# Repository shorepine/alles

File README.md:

# Alles - the mesh synthesizer

 [ **Chat about Alles on our Discord!**](https://discord.gg/TzBFkUb8pG)

**Check out this video!**

**Alles** is a many-speaker distributed mesh synthesizer that responds over WiFi. Each synth -- there can be hundreds in a mesh -- supports up to 120 additive oscillators, with filters, modulation / LFOs and ADSRs per oscillator. The mesh of speakers can be composed of any combination of our custom hardware speakers or programs running on computers. The software and hardware are open source: you can build it yourself or buy a PCB from us. 

The synthesizers automatically form a mesh and listen to multicast WiFi messages. You can control the mesh from a host computer using any programming language or environments like Max or Pd. 

We intended their first use as distributed / spatial version of an [Alles Machine](https://en.wikipedia.org/wiki/Bell_Labs_Digital_Synthesizer) / [Atari AMY](https://www.atarimax.com/jindroush.atari.org/achamy.html) additive synthesizer where each speaker represents up to 64 partials, all controlled as a group or individually. But you can just treat them as dozens of individual synthesizers and do whatever you want with them. It's pretty fun!

Want to try it today? [Build your own Alles](#diy-alles), or [install the software version](#using-it----software-alles
), and then read our [getting started tutorial!](https://github.com/shorepine/alles/tree/main/getting-started.md)

## Synthesizer specs

Each individual synth is powered by the [AMY synthesizer library](https://github.com/shorepine/amy/blob/main/README.md), you can read more details there. 

## Using it -- hardware Alles

On first boot, each hardware speaker will create a captive wifi network called `alles-synth-X` where X is some ID of the synth. Join it (preferably on a mobile device), and you should get redirected to a captive wifi setup page. If not, go to `http://10.10.0.1` in your browser after joining the network. Once you tell each synth what the wifi SSID and password you want it to join are, it will reboot. You only need to do that once per synth.

## Using it -- software Alles

If you don't want to build or buy an Alles speaker, you can run Alles locally on your computer(s), as many as you want. As long as each copy of the software is running within the same network, they will automatically form in the mesh just like the hardware speakers. And the hardware and software speakers can be used interchangeably.

To build and run `alles` on a computer, simply clone this repository and

```bash
$ cd alles/main
$ make
$ ./alles
$ ./alles -h # shows all the useful commandline parameters, like changing which channel/sound card, or source IP address
```

## Controlling the mesh

**Check out our brand new [Getting Started](https://github.com/shorepine/alles/tree/main/getting-started.md) page for a tutorial!**

You can control every synth on the mesh from a single host, using UDP over WiFi. You can address any synth in the mesh or all of them at once with one message, or use groups. This method can be used in music environments like Max or Pd, or by musicians or developers using languages like Python, or for plug-in developers who want to bridge Alles's full features to DAWs.

Alles's wire protocol is a series of numbers delimited by ascii characters that define all possible parameters of an oscillator. This is a design decision intended to make using Alles from any sort of environment as easy as possible, with no data structure or parsing overhead on the client. It's also readable and compact, far more expressive than MIDI and can be sent over network links, UARTs, or as arguments to functions or commands. 

Alles accepts commands in ASCII, each command separated with a `Z` (you can group multiple messages in one, to avoid network overhead if that's your transport). Like so:

```
v0w4f440.0l0.9Z
```

See [AMY's readme](https://github.com/shorepine/amy/blob/main/README.md) for the full list of synth parameters.

## alles.py 

Alles comes with its own full-featured client, written in Python. Feel free to adapt it or use it in your own clients. It can be seen as documentation, an API as well as a testing suite. You simply `import alles` and can control the entire mesh.

```bash
$ python3
>>> import alles
>>> alles.drums() # plays a drum pattern on all synths
>>> alles.drums(client=2) # just on one 
```

To see more examples, check out our brand new [Getting Started](https://github.com/shorepine/alles/tree/main/getting-started.md) page.

## Addressing individual synthesizers

By default, a message is played by all booted synthesizers. But you can address them individually or in groups using the `client` parameter.

The synthesizers form a mesh that self-identify who is running. They get auto-addressed `client_id`s starting at 0 through 255. The first synth to be booted in the mesh gets `0`, then `1`, and so on. If a synth is shut off or otherwise no longer sends a heartbeat signal to the mesh, the `client_ids` will reform so that they are always contiguous. A synth may take 10-20 seconds to join the mesh and get assigned a `client_id` after booting, but it will immediately receive messages sent to all synths. 

The `client` parameter wraps around given the number of booted synthesizers to make it easy on the composer. If you have 6 booted synths, a `client` of 0 only reaches the first synth, `1` only reaches the 2nd synth, and a client of `7` reaches the 2nd synth (`7 % 6 = 1`). 

Setting `client` to a number greater than 255 allows you to address groups. For example, a `client` of 257 performs the following check on each booted synthesizer: `my_client_id % (client-255) == 0`. This would only address every other synthesizer. A `client` of 259 would address every fourth synthesizer, and so on.

You can read the heartbeat messages on your host if you want to enumerate the synthesizers locally, see `sync` below. 

## Timing & latency

Alles is not designed as a low latency real-time performance instrument, where your actions have an immediate effect on the sound. Changes you make on the host will take a fixed latency -- currently set at 1000ms by default -- to get to every synth. This fixed latency ensures that messages arrive to every synth -- both ESP32 based and those running on computers -- in the mesh in time to play in perfect sync, even though Wi-Fi's transmission latency varies widely. This allows you to have millisecond-accurate timing in your performance across dozens of speakers in a large space.

Your host should send along the `time` parameter of the relative time when you expect the sound to play. I'd suggest using the number of milliseconds since your host started, e.g. in Python:

```python
def millis():
    d = datetime.datetime.now()
    return int((datetime.datetime.utcnow() - datetime.datetime(d.year, d.month, d.day)).total_seconds()*1000)
```

If you're using `alles.py`, we do this for you!

If using Max, use the `cpuclock` object as the `time` parameter.

The first time you send a message with `time` the synth mesh uses it to figure out the delta between its time and your expected time. (If you never send a time parameter, you're at the mercy of WiFi jitter.) Further messages will be millisecond accurate message-to-message, but with the fixed latency. You can adapt `time` per client if you want to account for speed-of-sound delay. 

The `time` parameter is not meant to schedule things far in the future on the clients. If you send a new `time` that is outside 20,000ms from its expected delta, the clock base will re-compute. Your host should be the main "sequencer" and keep track of performance state and future events. 

Latency is adjustable, if you are comfortable with your network you can set it lower, or if using a local (127.0.0.1) connection, or directly sending messages in code, you can set it to 0. 

## Enumerating synths

The `sync` command (see `alles.sync()`) triggers an immediate response back from each on-line synthesizer. The response looks like `_s65201i4c248y2`, where s is the time on the client, i is the index it is responding to, y has battery status (for versions that support that) and c is the client id. This lets you build a map of not only each booted synthesizer, but if you send many messages with different indexes, will also let you figure the round-trip latency for each one along with the reliability. 

## WiFi & reliability for performances

UDP multicast is naturally 'lossy' -- there is no guarantee that a message will be received by a synth. Depending on a lot of factors, but most especially your wireless router and the presence of other devices, that reliability can sometimes go as low as 70%. For performance purposes, I highly suggest using a dedicated wireless router instead of an existing WiFi network. You'll want to be able to turn off many "quality of service" features (these prioritize a randomly chosen synth and will make sync hard to work with), and you'll want to in the best case only have synthesizers as direct WiFi clients. An easy way to do this is to set up a dedicated wireless router but not wire any internet into it. Connect your laptop or host machine to the router over a wired connection (via a USB-ethernet adapter if you need one), but keep your laptop's wifi or other internet network active. In your controlling software, you simply set the source network address to send and receive multicast packets from. `alles_util.py` has setup code for this. This will keep your host machine on its normal network but allow you to control the synths from a second interface.

If you're in a place where you can't control your network, you can mitigate reliability by simply sending messages N times. Sending multiple duplicate messages (with the same `time` parameter) do not have any adverse effect on the synths.

## Clients

Minimal Python example:

```python
import socket
multicast_group = ('232.10.11.12', 9294)
sock = socket.socket(socket.AF_INET, socket.SOCK_DGRAM)

def send(oscillator=0, freq=0, vel=1):
    sock.sendto("v%df%fl%fZ" % (oscillator, freq, vel), multicast_group)

def c_major(octave=2):
    send(oscillator=0,freq=220.5*octave)
    send(oscillator=1,freq=138.5*octave)
    send(oscillator=2,freq=164.5*octave)

```

See [`alles.py`](https://github.com/shorepine/alles/blob/main/alles.py) for a better example. Any language that supports sockets and multicast can work, I encourage pull requests with new clients!

You can also easily use it in Max or Pd:

# Synthesizer Details

See [AMY's readme](https://github.com/shorepine/amy/blob/main/README.md) for more details on the synthesizer itself.

# Get your own Alles!

**[Read here how to install a PCB into a speaker shell!](speaker-assembly.md)**

If you want the small circular speakers shown on this page and videos, they are easy to get. Here's a link to them on Alibaba: [the round A60s](https://www.alibaba.com/product-detail/A60-Wooden-Grain-Portable-Wireless-Bluetooth_1600291216741.html?spm=a2700.wholesale.0.0.3e6c344biON4Qa) – the [square-shaped A70s](https://www.alibaba.com/product-detail/A70-Wood-Speaker-Grain-Portable-Wireless_1600291333969.html) also work! You then can buy an Alles PCB from us with no terminals for speaker and battery -- the connections for the shell solder directly to the board. It takes me about 3 minutes to assemble the Alles PCB inside the A60 or A70 speaker. To do it this way, you only need a wire stripper, a small screwdriver and a soldering iron. 
 
**IMPORTANT:** Alles is sold on a "best effort" community support basis. We will send you working PCBs with the latest Alles firmware loaded on them. Anything that happens after that is up to the community to help with. Alles requires a little bit of computer and networking know-how to get going. We've made it as easy as possible, we hope, but we know we have more work to do before this is ready for a very wide audience. Please use GitHub issues for anything you're having trouble with and we'll do our best to help you figure it out. 

## DIY Alles

It's very simple to make one yourself with parts you can get from electronics distributors like Sparkfun, Adafruit or Amazon. 

To make an Alles synth yourself, you need

* [ESP32 dev board (any one will do, but you want pins broken out)](https://www.amazon.com/gp/product/B07Q576VWZ/) (pack of 2, $7.45 each). Try to get a 8MB flash on yours if you want to have over-the-air updating.
* [The Adafruit I2S mono amplifier](https://www.adafruit.com/product/3006) ($5.95)
* [4 ohm speaker, this one is especially nice](https://www.parts-express.com/peerless-by-tymphany-tc6fd00-04-2-full-range-paper-cone-woofer-4-ohm--264-1126?gclid=EAIaIQobChMIwcX3-vXi5wIVgpOzCh0a7gjuEAYYASABEgLwf_D_BwE) ($9.77, but you can save a lot of money here going lower-end if you're ok with the sound quality). I also like speakers with prebuilt cases, like [these bookshelf speakers](https://www.amazon.com/Pyle-PCB3BK-100-Watt-Bookshelf-Speakers/dp/B000MCGF1O/ref=sr_1_1?dchild=1&keywords=pyle+home+speaker&qid=1592156929&s=electronics&sr=1-1).
* A breadboard, custom PCB, or just some hookup wire!

A 5V input (USB battery, USB input, rechargeable batteries direct to power input) powers both boards and speaker at pretty good volumes. A 3.7V LiPo battery will also work, but note the I2S amp will not get as loud (without distorting) if you give it 3.7V. If you want your DIY Alles to be portable, I recommend using a USB battery pack that does not do [low current shutoff](https://www.element14.com/community/groups/test-and-measurement/blog/2018/10/15/on-using-a-usb-battery-for-a-portable-project-power-supply). The draw of the whole unit at loud volumes is around 90mA, and at idle 40mA. 

Wire up your DIY Alles like this (I2S -> ESP)

```
LRC -> GPIO25
BCLK -> GPIO26
DIN -> GPIO27
GAIN -> I2S Vin (i jumper this on the I2S board)
SD -> not connected
GND -> GND
Vin -> Vin / USB / 3.3 (or direct to your 5V power source)
Speaker connectors -> speaker
```

### DIY bridge PCB

*You don't need this PCB made to build a DIY Alles!* -- it will work with just hookup wire. But if you're making a lot of DIY Alleses want more stability, I had a tiny little board made to join the boards together, like so:

This assumes you're using the suggested ESP32 dev board with its pin layout. If you use another one, you can probably change the GPIO assignments in `alles.h`. Fritzing file in the `pcbs` folder of this repository, and [it's here on Aisler](https://aisler.net/p/TEBMDZWQ). This is a lot more stable and easier to wire up than snipping small bits of hookup wire, especially for the GAIN connection. 

## Disabling OTA for 4MB boards

If you are using your own dev board and it has less than 8MB of flash (4MB is common), first overwwrite `alles_partitions.csv` with the contents of`alles_4mb_partitions.csv` as well as run `idf.py menuconfig` and change the flash size from 8MB to 4MB (in Serial Flasher Config) -- this will disable the OTA firmware upgrading, but will otherwise work fine. The binary for Alles is almost 4MB total and OTA needs space for two copies to be stored on the flash.

## ESP32 Firmware

Alles is completely open source, and can be a fun platform to adapt beyond its current capabilities. 

You can upgrade the firmware or write your own using the USB connection. [See the guide on flashing a hardware Alles speaker](https://github.com/shorepine/alles/tree/main/alles-flashing.md) (either DIY or one of ours). 

## THANK YOU TO

* Alles would not be possible without the help of [DAn Ellis](https://research.google/people/DanEllis/), who helped me with most of the oscillator stack, a lot of deep dives into our algorithm synth, and many great ideas / fixes on the ESP32 code.
* Douglas Repetto
* [Raph Levien](https://www.levien.com) for his work on [MSFA](https://github.com/google/music-synthesizer-for-android) which gave us a lot of hints for our FM implementation
* mark fell
* [esp32 WiFi Manager](https://github.com/tonyp7/esp32-wifi-manager)
* kyle mcdonald 
* Matt Mets / [Blinkinlabs](https://blinkinlabs.com)

## TODO

* ~~power button~~
* ~~wifi setup should ask for default power saving / latency -- no for now~~
* ~~remove distortion at higher amplitudes for mixed sine waves~~
* ~~FM~~
* ~~should synths self-identify to each other? would make it easier to use in Max~~
* ~~see what you can do about wide swings of UDP latency on the netgear router~~
* ~~envelopes / note on/offs / LFOs~~
* ~~confirm UDP still works from Max/Pd~~
* ~~bandlimit the square/saw/triangle oscillators~~
* ~~karplus-strong~~ 
* ~~wifi hotspot mode for in-field setup~~
* ~~broadcast UDP for multiples~~
* ~~dropped packets~~
* ~~sync and enumerate across multiple devices~~
* ~~addresses / communicate to one or groups, like "play this on half / one-quarter / all"~~
* ~~do what i can about timing / jitter - sync time? timed messages?~~
* ~~case / battery setup~~
* ~~overloading the volume (I think only on FM) crashes~~
* ~~UDP message clicks~~
* desktop USB flasher
* BT / app based config instead of captive portal (later)

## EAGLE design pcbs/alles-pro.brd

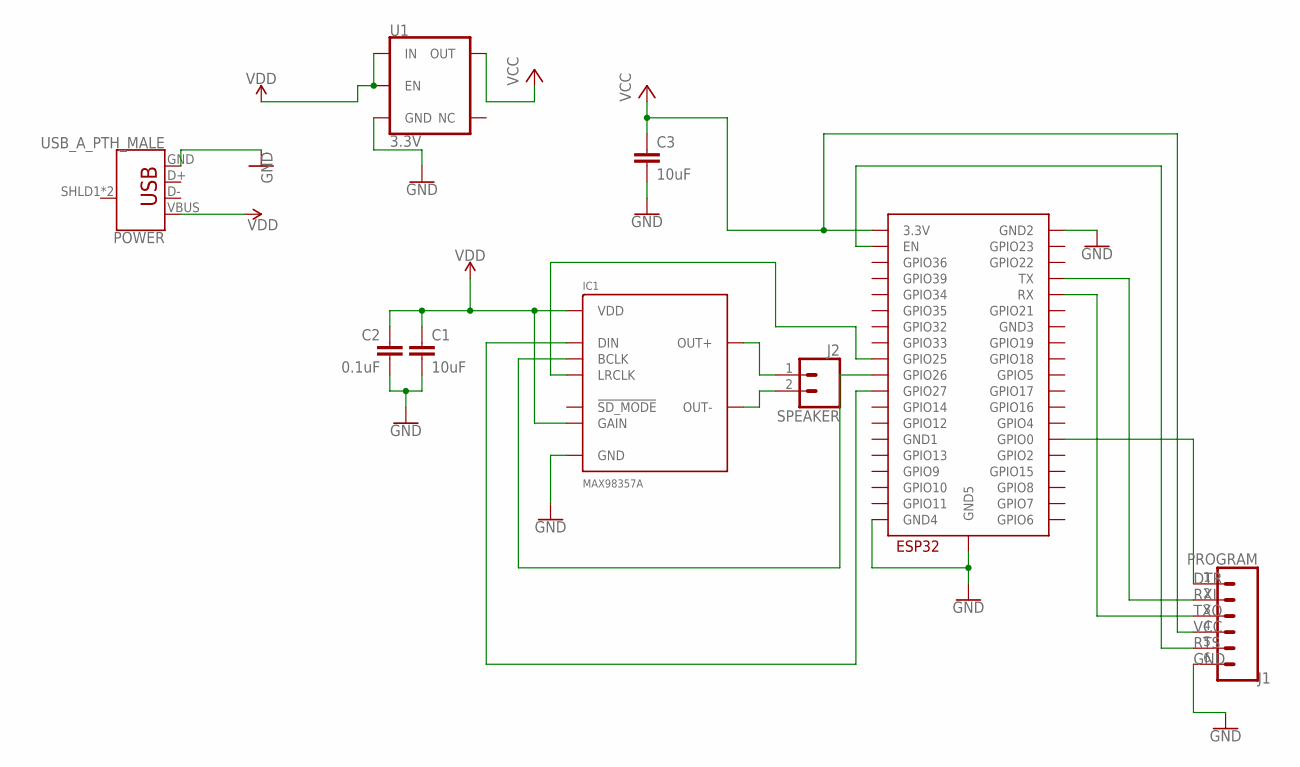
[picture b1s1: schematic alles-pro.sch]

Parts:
C1: 10uF; 0805
C2: 0.1uF; 0603
C3: 10uF; 0603
IC1: MAX98357A; TQFN-16
J1: PROGRAM; 1X06
POWER: USB_A_PTH_MALE; USB-A-H
SPEAKER: J2; SCREWTERMINAL-3.5MM-2-NS
U1: 3.3V; SOT23-5
U$21: ESP32-WROOM

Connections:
BCLK: IC1.P$16 (BCLK), U$21.IO26 (GPIO26)
DIN: IC1.P$1 (DIN), U$21.IO27 (GPIO27)
DTR: J1.1, U$21.IO0 (GPIO0)
GND: C1.2, C2.2, C3.2, IC1.P$3 (GND), IC1.P$11 (GND), IC1.P$15 (GND), IC1.P$EP (GND), J1.6, POWER.GND, U1.2 (GND), U$21.GND2, U$21.GND4, U$21.GND5
LRCLK: IC1.P$14 (LRCLK), U$21.IO25 (GPIO25)
OUT+: IC1.P$9 (OUT+), SPEAKER.1
OUT-: IC1.P$10 (OUT-), SPEAKER.2
RTS: J1.5, U$21.EN
RXI: J1.2, U$21.TX
TXO: J1.3, U$21.RX
VCC: C3.1, J1.4, U1.5 (OUT), U$21.3V3 (3.3V)
VDD: C1.1, C2.1, IC1.P$2 (GAIN), IC1.P$7 (VDD), IC1.P$8 (VDD), POWER.VBUS, U1.1 (IN), U1.3 (EN)

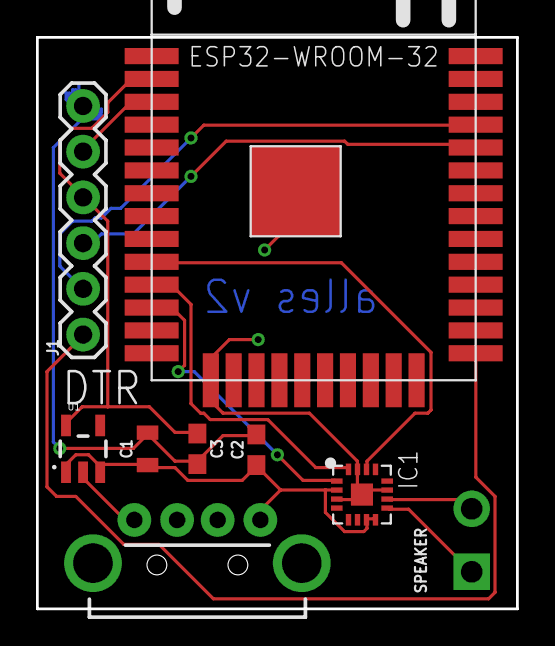
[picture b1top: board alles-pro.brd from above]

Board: 2 copper layers, 26.7 x 31.7 mm, 9 parts (0 on the bottom side), 12 nets.

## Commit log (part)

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2021-04-20 Miller's cubic interp optimization; Real pulse wave with PWM
2021-04-21 removing DANDAC as dan has a better way
2021-04-22 Minor proposal (line 161)
2021-04-24 Reconfig i2s output for external dac
2021-04-24 global.volume and cubic soft clipping
2021-04-25 Add soft clip; remove blip_buffer; fix ESP32 LEFT_ONLY word shuffle.
2021-04-25 Cubic interpolation of LUT; shorter sine LUT; added impulse LUT; pulse PWM as integrated difference of impulses.
2021-04-25 Linear interp by default; SAW and TRIANGLE also bandlimited; Waveforms constructed in scratchbuf; Waveform amplitudes equalized across shapes and frequencies.
2021-04-27 multicore rendering. voices=8, cubic, 240Mhz
2021-04-27 no blip
2021-04-28 oscillator -> c
2021-04-28 adding dan's make_lut
2021-04-28 stop tying debug voices to volume
2021-04-28 make_lut > 4 spaces
2021-04-28 voices=8
2021-04-29 debug voices -> D
2021-04-29 voice -> oscillator
2021-05-01 dumb lfo bug
2021-05-02 LFOs now run at SR=44100/64
2021-05-02 bug in one lfo
2021-05-06 revB power & buttons
2021-05-06 adding power.
2021-05-07 battery state
2021-05-07 only 2 simultaneous KS oscillators for RAM
2021-05-07 midi mode works again. better sounds. buttons work on revB.
2021-05-08 reset osc after startup
2021-05-08 use osc, it's cleaner
2021-05-08 oscillator rendering one per osc, better CPU usage handler
2021-05-08 making new style work, fit in ram
2021-05-09 parameterizing # of cores for CPU testing
2021-05-09 dumb bug on split renderer
2021-05-09 more testing, but can do 28 linear oscillators on one chip now
2021-05-09 24 voices not bad
2021-05-10 moving defines
2021-05-10 trying to detect devboard
2021-05-10 back to osc.cc until brian passes CS101
2021-05-10 make_lut now in alles_util
2021-05-10 adding smaller LUTs and LUT generator
2021-05-10 64 oscillators, removing floor, one FM patch for mem for now
2021-05-10 Readme
2021-05-10 debug showing less data
2021-05-13 more efficient event handling, start of partial decoding
2021-05-13 fixing delta bug, better usage reporting
2021-05-14 removing strict aliasing warning
2021-05-14 wrapping access to the queue in a mutex
2021-05-14 show messages/events received in debug
2021-05-15 buffer multiple UDP messages, can get about 3000 / second now
2021-05-17 filters work per oscillator now
2021-05-19 eq, (thanks dan!) 3 filter types, renaming LFO->mod
2021-05-22 Soft clipping by lookup table (#10).
2021-05-22 checkpoint for FM
2021-05-22 fixing git mash and removing make_lut, we already have it
2021-05-22 make_clipping_lut now in alles_util
2021-05-23 Pitch-adaptive lookup tables; Triangle has its own tables.
2021-05-23 the price of dpwe's expert labor is having to convert his 2 spaces to 4
2021-05-23 CPU usage via GPIO & simpler buffering in alles_util
2021-05-23 make_lutsets.py creates the LUTset header files.
2021-05-23 lut sets, cleaning up old luts
2021-05-24 dan threatened me with a style guide
2021-05-25 No more cumulative mixing, fixed filters, sine LUT starts in the right place
2021-05-25 Higher priority i2s, ADSR is now a sample clock
2021-05-28 quad buffering to avoid clicks
2021-05-28 sample type
2021-06-06 We don't need beta, that's per-operator amp, same thing
2021-06-07 refactor Alles to use libAMY
2021-06-07 adding AMY
2021-06-07 local AMY working, no more esp-dsp
2021-06-07 Local AMY mode works more reliably
2021-06-08 more AMY
2021-06-08 readmes
2021-06-09 checkpoint for dan
2021-06-09 lut w/ feedback
2021-06-11 FM patch converter in progress
2021-06-11 fixing feedback for FM
2021-06-11 AMY local / rendering
2021-06-13 DX7 algorithms should work, more work to do on envelopes
2021-06-13 splitting out AMY from alles
2021-06-13 ADSR bugs fixed up, getting there on our own FM impl
2021-06-13 start breakpoint
2021-06-13 Moving ADSR to breakpoints. Still some issues with ALGO type but the base things work
2021-06-14 fixing the bp parser
2021-06-14 docs
2021-06-14 readme loc
2021-06-14 comments
2021-06-14 Some fixes to the FM conversion.
2021-07-06 partials update
2021-07-06 adding header generator and wavdumper for partial computation
2021-07-06 First stab at a PARTIAL type for bandwidth-excited sines
2021-07-06 moving scratch to stack
2021-07-06 better partial
2021-07-09 much better partial synth
2021-07-10 bandwidth enhanced partials
2021-07-10 partial header writer
2021-07-10 partials.c
2021-07-10 partials.h / .c
2021-07-10 adsr -> breakpoint
2021-07-10 out_buf warning
2021-07-11 first pass at partials.c
2021-07-11 fixes
2021-07-11 better queue
2021-07-11 deque
2021-07-11 checkpoint
2021-07-12 better
2021-07-12 better map
2021-07-12 partials
2021-07-12 fix struct
2021-07-12 cleaning
2021-07-12 fix partials
2021-07-15 adding loris and instructions for loris
2021-07-17 fixed to fm
2021-07-17 FM patch loading
2021-07-17 fixed
2021-07-17 fixed up, saved 88 FM patches
2021-07-18 partial/partials cleanup. release special case for partial type
2021-07-18 three working BP targets
2021-07-20 Alles desktop
2021-07-20 Automatically get the first IP
2021-07-20 remove debug
2021-07-22 circular imports , cleaning up sync
2021-07-23 fixed up sync to honor predicted time
2021-07-24 fitting partials into esp32, some other similar changes
2021-07-24 moving plt import off
2021-07-25 cleaning up on esp32
2021-07-25 let people turn off the speaker while it's searching for wifi
2021-07-25 test midi bridge
2021-07-25 fixing up virtualmidi tester
2021-07-25 chasing down a crackle on the i2s but getting there
2021-07-26 no more crackle
2021-07-26 sync fixes; power monitor works on revB boards again
2021-07-27 allowing mac desktop alles to receive midi (for debugging, not sure if we want this as a feature yet)
2021-07-30 midi mode pressed during wifi wait
2021-07-31 getting started guide
2021-07-31 getting started pics
2021-07-31 smaller
2021-07-31 off-by-one error in algorithm #
2021-07-31 cleaning up imports
2021-07-31 more getting started
2021-07-31 adding pic
2021-08-01 more FM patches, delimit via Z instead of newline
2021-08-01 partials play locally again
2021-08-01 remvoing debug
2021-08-02 retrigger breakpoints on breakpoint changes
2021-08-02 cleaning up amy/alles.py
2021-08-02 sync returning the Z
2021-08-06 newer IDF on the linux box, fixing up some compiler issues there too
2021-08-06 adding pics
2021-08-07 partials pic
2021-08-10 fixed up a lot of soundio badness, and allowed to set channels & device ID at the CL for local Alles
2021-08-11 more sounds in the PCM bucket, need to add loops and choose these better
2021-08-11 moving PCM to its own file
2021-08-14 stable PCM looping
2021-08-14 smoothed amplitude & writing raw files on desktop
2021-08-15 fixing up the patches for new PCM bank
2021-08-27 new sound
2021-08-27 readme test
2021-08-27 also interp amp for AM and FM
2021-09-05 removing AMY
2021-09-05 readmes, cleaning up AMY/Alles
2021-09-05 removing AMY readme
2021-09-05 longer wifi wait time
2021-09-05 KS note
2021-09-06 more readme
2021-09-15 remove TODO
2021-09-17 better max patch
2021-09-17 replacing max pic
2021-10-08 removing BLE. fixing benL's issue
2021-10-08 Minor fix (paragraph 44)
2021-10-09 removing MIDI mode (in lieu of host control) + volume on speaker
2021-10-10 More fully removing on-device MIDI; this will be moved to software alles as a relay
2021-10-12 midi mode/tones
2021-11-11 douglas's error, some new idf stuff
2021-11-24 Moving PCM to a partition on chip to save room. Removing partials presets.
2021-11-24 Adding pcm
2021-11-24 Explain how to flash the LUT partition
2021-11-24 adding baked alles.bin for ota
2021-11-26 OTA working
2021-11-26 putting fm back
2021-11-26 new version release to OTA
2021-11-26 partition change
2021-11-27 putting partials back, OTA has LUTs baked in
2021-11-27 new ota
2021-11-27 ota version checking
2021-11-30 fixing volume and multicast TTL
2021-12-03 better max patches, still a work in progress
2021-12-03 preset
2021-12-04 details on flashing
2021-12-04 adding 4mb
2021-12-05 douglas repetto jam
2021-12-05 just checking latest ota
2021-12-12 thank you thor
2021-12-17 removing alles flasher, no longer needed
2022-06-17 fm playback
2022-06-19 fixing #25
2022-06-19 remvoing VM
2022-06-19 new feature for dan
2022-06-20 making this easier
2022-06-21 Improvements to DX7 patch compatibility.
2022-06-21 fixing bp envelope to start at level4
2022-06-21 debugging
2022-06-21 much better algorithm setup
2022-06-22 dan's fixes to ratio and fixed frq
2022-06-22 timing
2022-06-22 schedling note off using alles timer, not python
2022-06-22 Modify fm.py patch processing to go via an intermediate structure with just plain parameters.
2022-06-22 fixing envelope release
2022-06-22 fence
2022-06-22 merged in Dan ellis's changes manually
2022-06-22 better measured LFO
2022-06-25 supprint TARGET_TRUE_EXPONENTIAL
2022-06-25 back to clamp at 20
2022-06-25 Update fm.py
    Remove whitespace diff from Whitman
2022-06-25 Fixing DX7 TRUE_EXPONENTIAL timing; incorporating new discoveries about interpretation of R1 (attack).
2022-06-25 algorithm starts at 1
2022-06-25 better LFO
2022-06-26 adding function to send patch data to my tx802 remotely for Dan
2022-06-27 Various changes, integrating improved attack-segment timing (but shape is wrong until we also change alles) and other bits.
2022-06-27 fixing dan's reported bug
2022-06-27 Avoid div0 for zero-length segments
    Maybe try this instead?
2022-06-27 fixing #31
2022-06-27 better nan detection
2022-06-27 elapsed check
2022-06-27 comments from dan
2022-06-27 raph's name
2022-06-27 Fold detune into freq ratio/fixedhz
    Untested but believed working. detune -7..7 simply subdivides the FINE frequency steps
2022-06-27 SAW directions in fm.py
2022-06-27 detune better
2022-06-28 Hacky, but release works
2022-06-28 Clipping table overrun fix.
2022-06-28 fixing issues on #34
2022-06-28 constants
2022-07-03 Convert patch structs in fm.py to dataclasses; stored fm algos in amy are 5-breakpoint.
2022-07-03 Added DX7 attack envelope type.
2022-07-03 random()
2022-07-03 patch playback
2022-07-03 type fixes to compile on Tulip easier
2022-07-04 Some missing/misnamed field definitions in fm.py:DX7Operator.
2022-07-04 Cleanup alles build for esp32
2022-07-04 pcm small vs big types
2022-07-04 adding baked PCM sizes
2022-07-04 Add dc-blocking HPF to final output.
2022-07-04 Add all-python DX7 emulation to fm.py.
2022-07-04 Moved pure-Python dx7 simulator to its own file.
2022-07-04 Added LFO for pitch and amp to dx7_simulator.
2022-07-05 fixing nan in envelope, no more pitch BPs per op
2022-07-05 Pitch envelope calculation fixed to match tx802, both fm.py and dx7_simulator.
2022-07-05 re-building fm patches
2022-07-06 adjustable latency
2022-07-06 no ifdef for latency
2022-07-06 trunc
2022-07-13 new OTA upgrade
2022-07-13 stack size
2022-09-12 updating submodule
2022-09-15 stage 2
2022-09-16 finished merging submodule-amy
2022-09-16 adding these
2022-09-16 mcast
2022-09-16 removing MIDI
2022-09-17 sync --> alles
2022-09-17 removing
2022-09-17 adding amy directly, no submodules
2022-09-26 v0.2-alpha ota
2022-10-23 better flashing instructions for #47
2022-10-23 adding revD pcbs from blinklabs
2022-12-03 change arg kw
2023-02-24 merging in new AMY + fixing extern
2023-02-25 readme change from #51
2023-03-29 Add docker-based build environment
2023-06-21 Update to latest amy (uses tinyaudio)
2023-06-22 dweb2023 materials
2023-06-23 fix for #56
2023-06-23 cleaning up libsoundio
2023-06-23 working on esp5.1-rc2
2023-06-26 working
2023-06-26 new OTA for 5.x idf
2023-07-01 fixing up amy module
2023-07-01 working ok
2023-07-01 submodule checkout
2023-07-01 working esp build
2023-07-02 makefile for rpi64, changes for mac build, changes to docs for clone only
2023-07-05 youtube video
2023-07-05 dweb
2023-07-23 Adding A60 speaker assembly guide
2023-09-18 Fix for #67
2023-12-09 amy desktop working on FXP
2023-12-09 alles esp32 fixes
2023-12-09 in progress, need to fix crasher
2023-12-10 alles esp32 works on fxp
2023-12-13 new amy branch
2024-06-09 upping submodule to latest AMY and adding new AMY sources. updating docs
2024-06-09 boots,needs work on stereo
2024-06-09 working juno6 (at least 6 poly) on alles
2024-06-09 seems to all work
2024-06-09 latest amy
2024-06-13 removing millis(), amy now has this
2024-06-13 upping amy
2024-06-19 new name
2024-11-02 working new computed_delta for alles
2024-11-02 fixing computed delta
2024-11-02 readme update
2024-11-04 new style of insert_time

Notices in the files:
parts and their libraries:
SparkFun-Capacitors: Licensing: Creative Commons ShareAlike 4.0 International - https://creativecommons.org/licenses/by-sa/4.0
